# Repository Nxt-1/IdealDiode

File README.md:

# IdealDiode

A small implementation around a TI LM74700 ideal diode controller.

Ideal diode controllers are an idealistic approximation of a diode one-way current blocking functionality. This is achieved by switching an N-channel MOSFET when conduction is desired and using the MOSFET's internal body diode to block current otherwise. The TI part monitors the input and output voltage and drives the transistor when current need to block (i.e. when V_IN > V_OUT).

By fully saturating the transitor's gate, the voltage drop source and drain is in the order of tens of milivolts instead of the typical 700mV for a silicon diode.

## Use Case

This project is designed to be used when charching multiple 36V nominal (42V max) lithium battery packs in parallel. Specifically batteries with separated charge port BMS, that are always energised. If no protection was implemented, connecting the batteries in parallel could cause the full battery current of a battery with a higher state of charge to flow through the other battery's chargeport. Using a regular diode would effectively lower the maximum charge voltage by the diode's voltage drop, thus decreasing the usable battery capacity. Hence the ideal diode circuit.

## Specifactions

The device is designed to withstand 42V nomimal and a charge current of 5A.

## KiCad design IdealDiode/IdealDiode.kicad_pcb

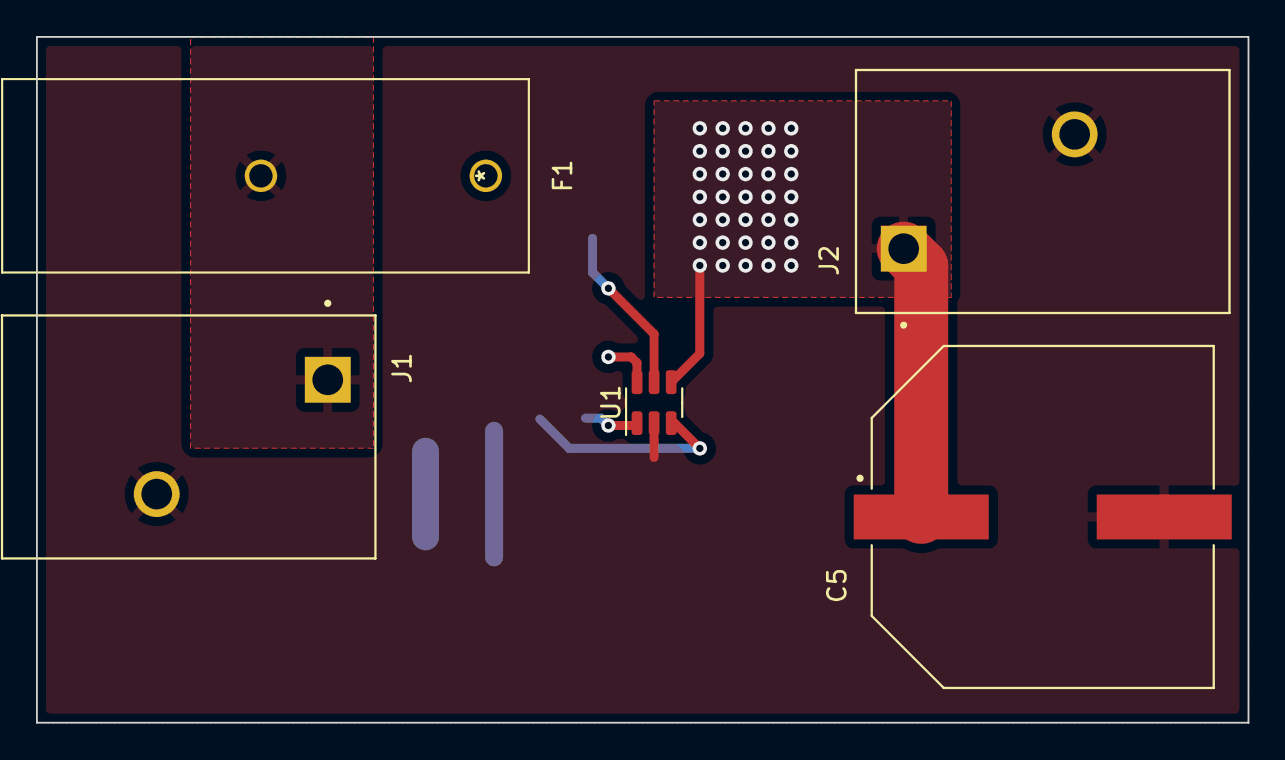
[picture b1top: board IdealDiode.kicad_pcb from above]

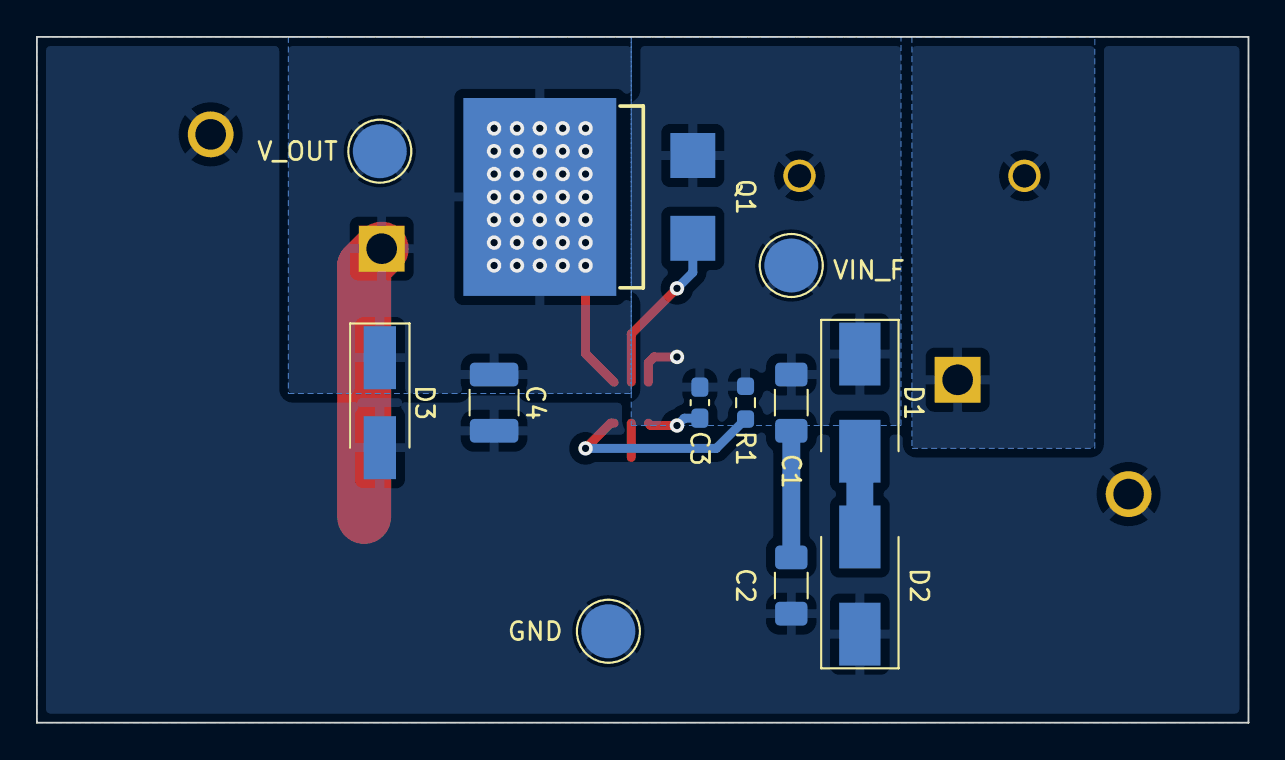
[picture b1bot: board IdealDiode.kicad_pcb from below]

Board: 2 copper layers, 67.3 x 38.1 mm, 17 parts (12 on the bottom side), 9 nets.

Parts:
C1, C2: 0.33µF; C_1206_3216Metric_Pad1.33x1.80mm_HandSolder
C3: 1µF; C_0603_1608Metric_Pad1.08x0.95mm_HandSolder
C4: 2.2µF; C_1210_3225Metric_Pad1.33x2.70mm_HandSolder
C5: 220µF; CAP_EEVFK2A221M
D1: SMBJ58A-13-F; D_SMB_Handsoldering
D2: SMBJ28A-13-F; D_SMB_Handsoldering
D3: SMAJ58A; D_SMA_Handsoldering
F1: FUSE_4525_KEY; 4525
GND: GND; TestPoint_Pad_D3.0mm
J1, J2: 1017521; PHOENIX_1017521
Q1: RSJ650N10TL; R6024KNJTL
R1: 0; R_0603_1608Metric_Pad0.98x0.95mm_HandSolder
U1: LM74700; SOT-23-6
VIN_F: VIN_F; TestPoint_Pad_D3.0mm
V_OUT: V_out; TestPoint_Pad_D3.0mm

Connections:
/EN: R1.2, U1.3 (EN)
/GATE: Q1.1, U1.5 (GATE)
/VIN: F1.2, J1.1
/VIN_F: C1.1, C3.1, D1.1 (K), F1.1, Q1.3, R1.1, U1.6 (ANODE), VIN_F.1
/VOUT: C4.1, C5.1, D3.1 (K), J2.1, Q1.2, U1.4 (CATHODE), V_OUT.1
GND: C2.2, C4.2, C5.2, D2.1 (K), D3.2 (A), GND.1, J1.2, J2.2, U1.2 (GND)
unnamed: C1.2, C2.1
unnamed: C3.2, U1.1 (VCAP)
unnamed: D1.2 (A), D2.2 (A)

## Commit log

2023-01-16 Updated readme to include project info
2023-01-16 Updated readme: specs
2023-01-16 License
2023-01-16 PCB files
2023-01-16 Manufacturing output
2023-01-16 Schematic pdf
